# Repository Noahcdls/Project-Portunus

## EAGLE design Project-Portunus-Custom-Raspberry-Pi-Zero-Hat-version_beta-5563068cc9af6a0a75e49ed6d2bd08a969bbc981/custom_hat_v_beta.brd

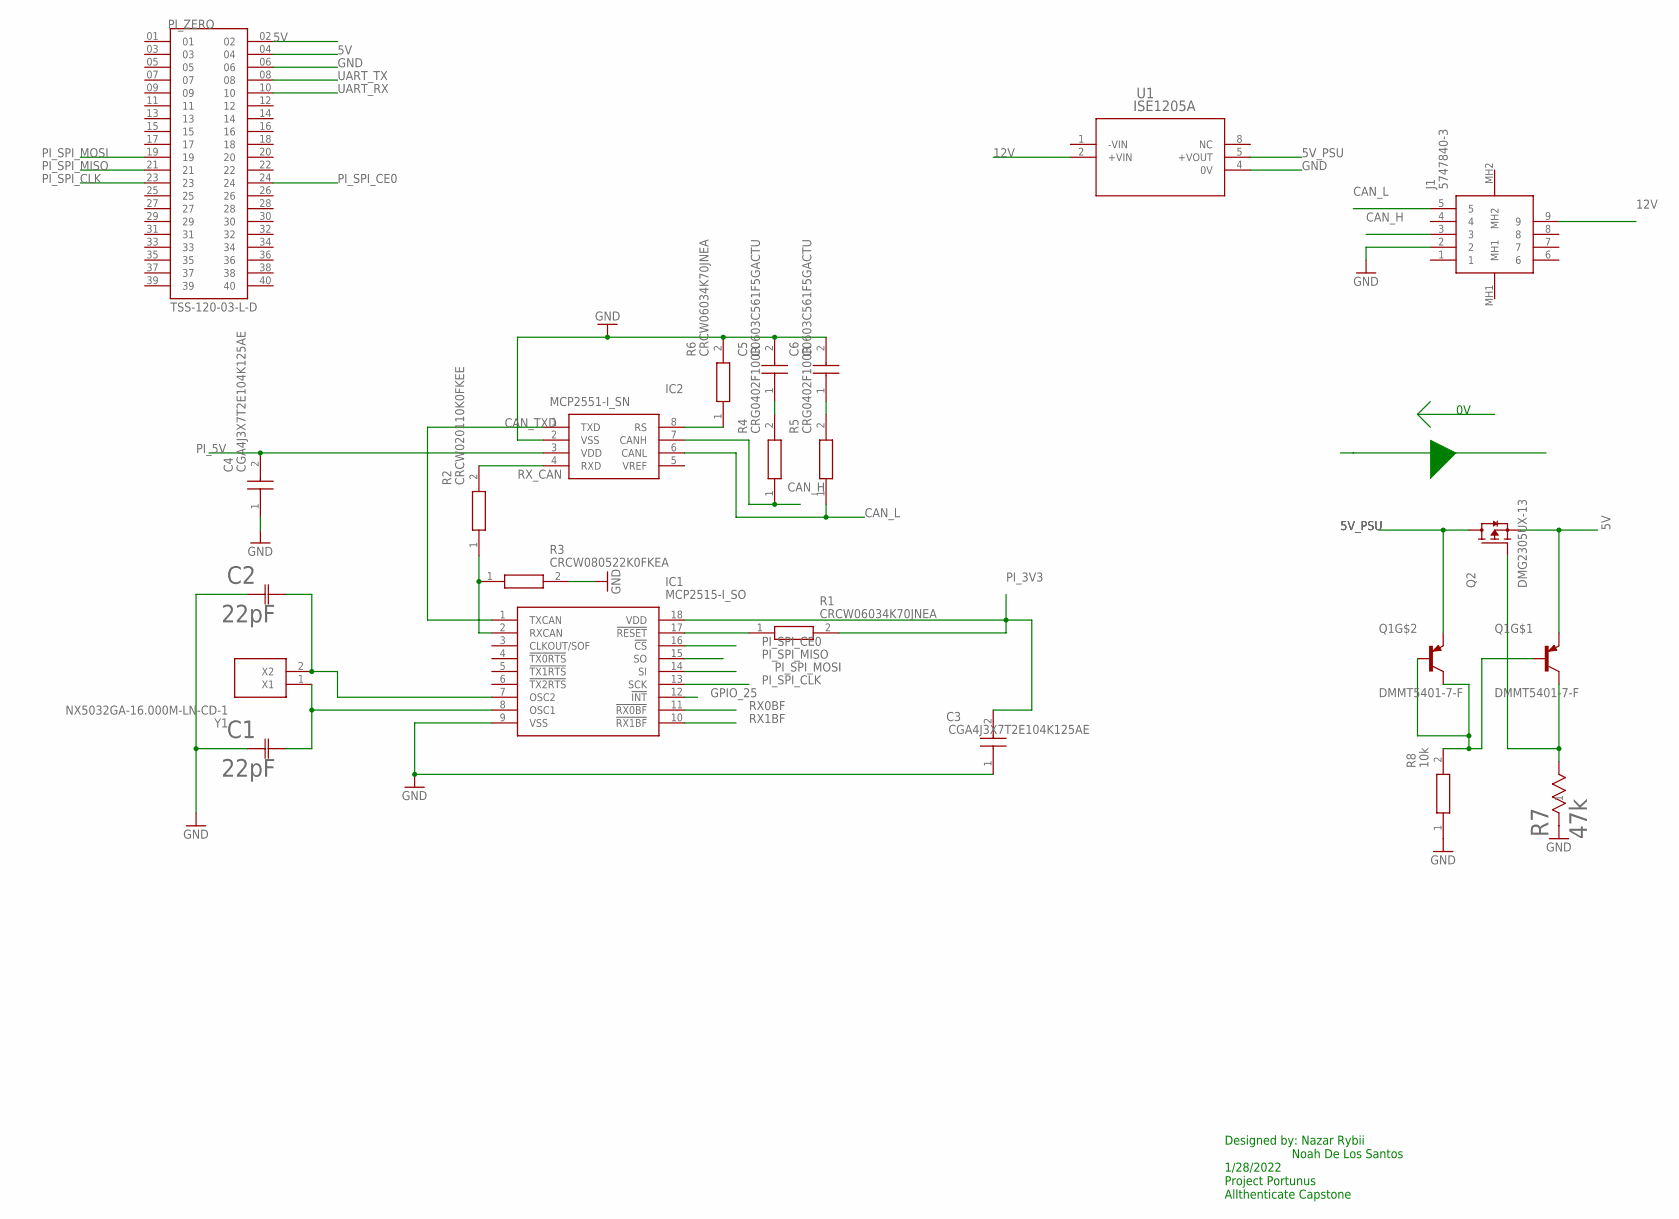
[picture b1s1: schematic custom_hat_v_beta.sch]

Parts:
C1, C2: 22pF; CAP_CL21_SAM
C3, C4: CGA4J3X7T2E104K125AE; CAPC2012X145N
C5, C6: C0603C561F5GACTU; CAPC1608X87N
IC1: MCP2515-I_SO; SOIC127P1030X265-18N
IC2: MCP2551-I_SN; SOIC127P600X175-8N
J1: 5747840-3; 57478403
PI_ZERO: TSS-120-03-L-D; SAMTEC_TSS-120-03-L-D
Q1: DMMT5401-7-F; SOT95P285X140-6N
Q2: DMG2305UX-13; SOT91P240X110-3N
R1, R6: CRCW06034K70JNEA; RESC1608X50N
R2: CRCW020110K0FKEE; RESC0603X28N
R3: CRCW080522K0FKEA; RESC2012X50N
R4, R5: CRG0402F100R; RESC1005X40N
R7: 47k; RC0603N_YAG
R8: 10k; RESC2012X50N
U1: ISE1205A; ISE1205A_XPP
Y1: NX5032GA-16.000M-LN-CD-1; NX5032GA16000000MHZLNCD1

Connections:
5V: PI_ZERO.02, PI_ZERO.04, Q1.6 (E), Q2.2 (S)
5V_PSU: Q1.5 (E), Q2.3 (D), U1.5 (+VOUT)
12V: J1.9, U1.2 (+VIN)
-VIN: U1.1 (-VIN)
CAN_H: IC2.7 (CANH), J1.3, R4.1
CAN_L: IC2.6 (CANL), J1.5, R5.1
CAN_TXD: IC1.1 (TXCAN), IC2.1 (TXD)
GND: C1.1, C2.1, C3.1, C4.1, C5.2, C6.2, IC1.9 (VSS), IC2.2 (VSS), J1.2, PI_ZERO.06, R3.2, R6.2, R7.1, R8.1, U1.4 (0V)
GPIO_25: IC1.12 (!INT)
unnamed: Q1.1 (C), Q2.1 (G), R7.2
unnamed: Q1.2 (B), Q1.3 (B), Q1.4 (C), R8.2
unnamed: IC1.2 (RXCAN), R2.1, R3.1
unnamed: IC2.8 (RS), R6.1
unnamed: C1.2, IC1.8 (OSC1), Y1.1 (X1)
unnamed: C2.2, IC1.7 (OSC2), Y1.2 (X2)
unnamed: C5.1, R4.2
unnamed: C6.1, R5.2
unnamed: IC1.17 (!RESET), R1.1
PI_3V3: C3.2, IC1.18 (VDD), R1.2
PI_5V: C4.2, IC2.3 (VDD)
PI_SPI_CE0: IC1.16 (!CS), PI_ZERO.24
PI_SPI_CLK: IC1.13 (SCK), PI_ZERO.23
PI_SPI_MISO: IC1.15 (SO), PI_ZERO.21
PI_SPI_MOSI: IC1.14 (SI), PI_ZERO.19
RX0BF: IC1.11 (!RX0BF)
RX1BF: IC1.10 (!RX1BF)
RX_CAN: IC2.4 (RXD), R2.2
UART_RX: PI_ZERO.10
UART_TX: PI_ZERO.08

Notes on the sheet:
Designed by: Nazar Rybii Noah De Los Santos 1/28/2022 Project Portunus Allthenticate Capstone

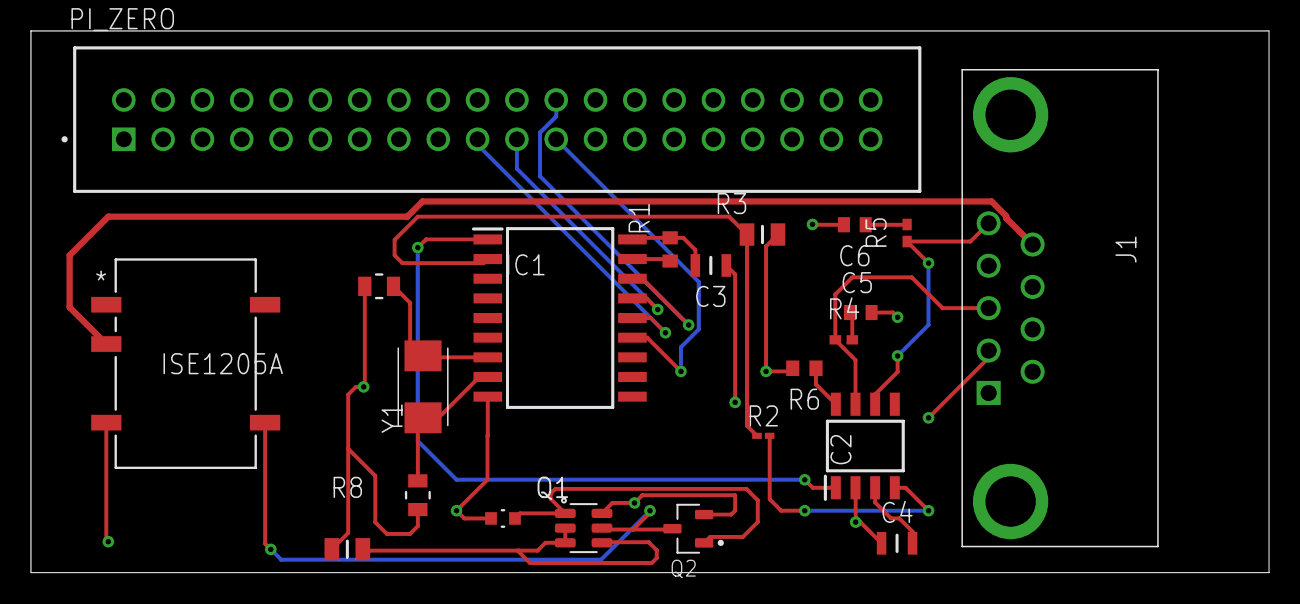
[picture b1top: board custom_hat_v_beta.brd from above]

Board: 4 copper layers, 80.0 x 35.0 mm, 22 parts (0 on the bottom side), 23 nets.

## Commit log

2022-06-05 Initial Diagnostics
2022-06-06 Beta Board
2022-06-06 GPS/GSM
2022-06-06 Newer files from pi
2022-06-06 Mobile App

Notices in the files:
parts and their libraries:
COPYRIGHT: Copyright (C) 2022 Ultra Librarian. All rights reserved.
